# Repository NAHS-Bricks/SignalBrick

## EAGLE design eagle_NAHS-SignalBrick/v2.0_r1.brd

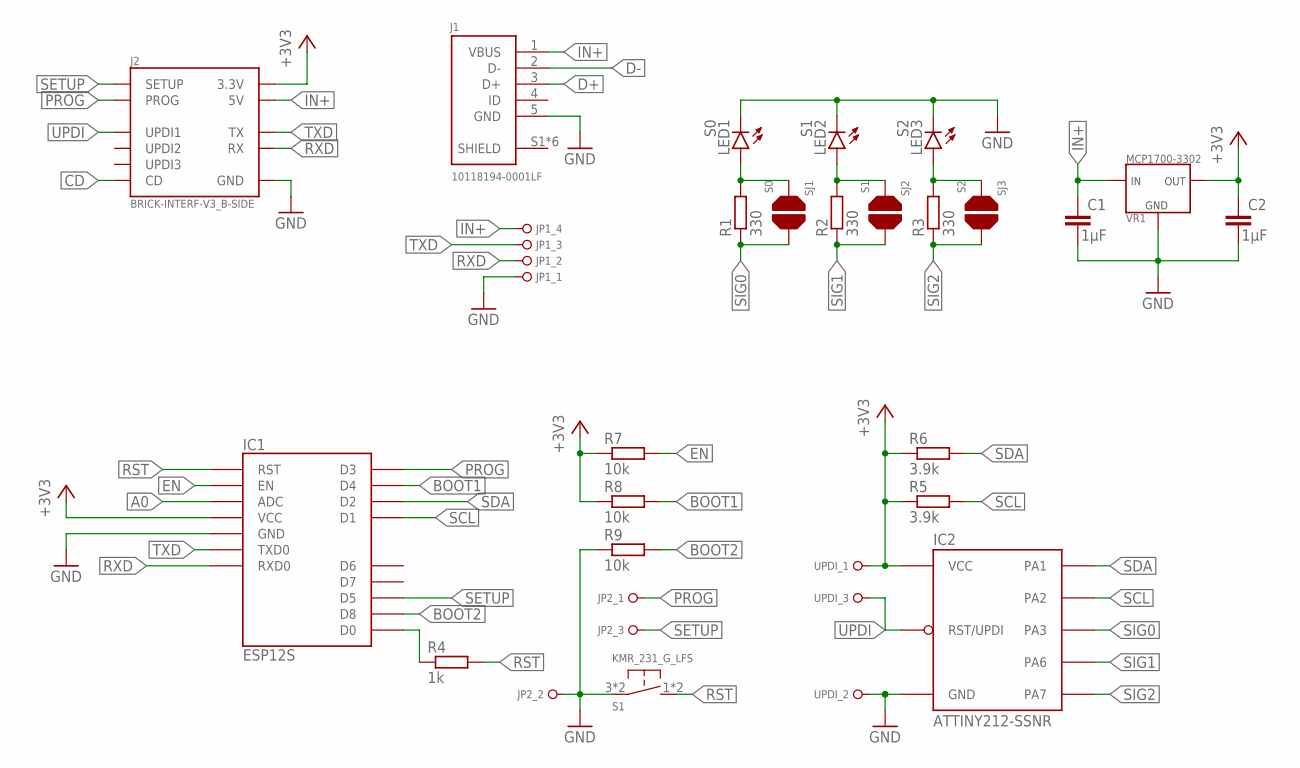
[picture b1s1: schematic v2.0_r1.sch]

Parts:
C1, C2: 1µF; C0805
IC1: ESP12S
IC2: ATTINY212-SSNR; SOIC8
J1: 10118194-0001LF
J2: BRICK-INTERF-V3_B-SIDE; DF9-11P-1V(32)
JP1: PINHD_1X04_R_1; 1X04_R_1
JP2: PINHD_1X03_R_1; 1X03_R_1
LED1: S0; LED5MM
LED2: S1; LED5MM
LED3: S2; LED5MM
R1, R2, R3: 330; R0603
R4: 1k; R0805
R5, R6: 3.9k; R0805
R7, R8, R9: 10k; R0805
S1: KMR_231_G_LFS
SJ1: S0; SOLDERJUMPER
SJ2: S1; SOLDERJUMPER
SJ3: S2; SOLDERJUMPER
UPDI: PINHD_1X03_R_1; 1X03_R_1
VR1: MCP1700-3302; SOT23

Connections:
+3V3: C2.1, IC1.VCC, IC2.1 (VCC), J2.10 (3.3V), R5.1, R6.1, R7.1, R8.1, UPDI.1, VR1.2 (OUT)
A0: IC1.ADC
BOOT1: IC1.GPIO2 (D4), R8.2
BOOT2: IC1.GPIO15 (D8), R9.2
CD: J2.5 (CD)
D+: J1.3 (D+)
D-: J1.2 (D-)
EN: IC1.EN, R7.2
GND: C1.2, C2.2, IC1.GND, IC2.8 (GND), J1.5 (GND), J2.6 (GND), JP1.1, JP2.2, LED1.K (C), LED2.K (C), LED3.K (C), R9.1, S1.3 (2), S1.4 (2), UPDI.2, VR1.1 (GND)
IN+: C1.1, J1.1 (VBUS), J2.4 (5V), JP1.4, VR1.3 (IN)
unnamed: LED1.A, R1.2, SJ1.1
unnamed: LED2.A, R2.2, SJ2.1
unnamed: LED3.A, R3.2, SJ3.1
PROG: IC1.GPIO0 (D3), J2.3 (PROG), JP2.1
RST: IC1.RST, R4.2, S1.1, S1.2 (1)
RXD: IC1.RXD0, J2.11 (RX), JP1.2
SCL: IC1.GPIO5 (D1), IC2.5 (PA2), R5.2
SDA: IC1.GPIO4 (D2), IC2.4 (PA1), R6.2
SETUP: IC1.GPIO14 (D5), J2.2 (SETUP), JP2.3
SHIELD: J1.S1 (SHIELD), J1.S2 (SHIELD), J1.S3 (SHIELD), J1.S4 (SHIELD), J1.S5 (SHIELD), J1.S6 (SHIELD)
SIG0: IC2.7 (PA3), R1.1, SJ1.2
SIG1: IC2.2 (PA6), R2.1, SJ2.2
SIG2: IC2.3 (PA7), R3.1, SJ3.2
TXD: IC1.TXD0, J2.1 (TX), JP1.3
UPDI: IC2.6 (RST/UPDI), J2.7 (UPDI1), UPDI.3
WAKE: IC1.GPIO16 (D0), R4.1

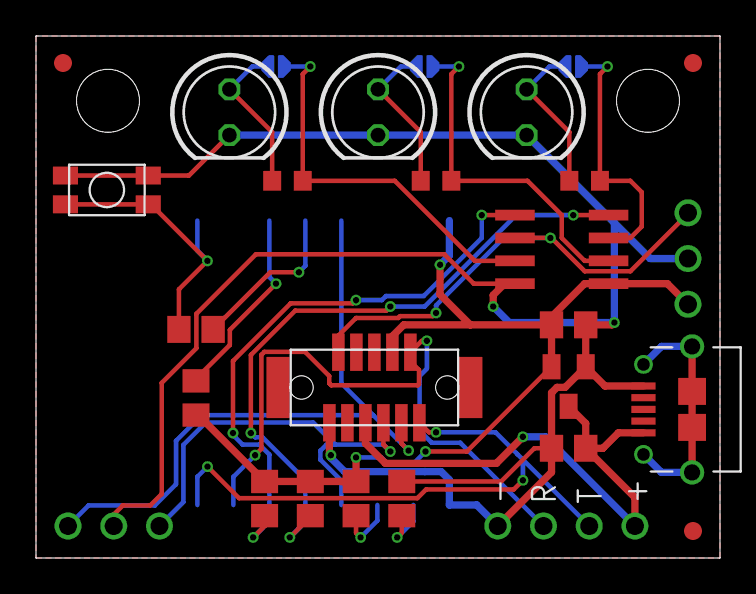
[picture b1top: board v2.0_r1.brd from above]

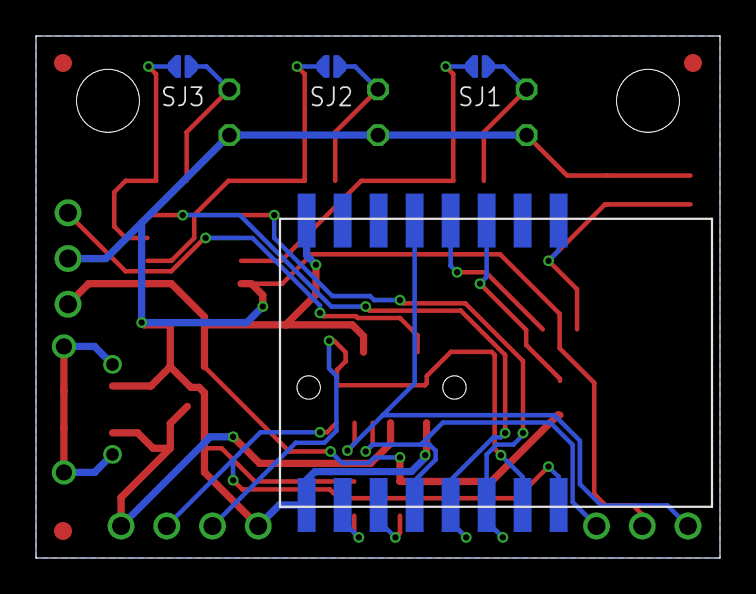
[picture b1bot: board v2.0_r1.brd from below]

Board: 2 copper layers, 38.0 x 29.0 mm, 30 parts (5 on the bottom side), 22 nets.

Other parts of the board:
FD1, FD2, FD3: FIDUCIAL
U$3: BRICKS_LOGO_10

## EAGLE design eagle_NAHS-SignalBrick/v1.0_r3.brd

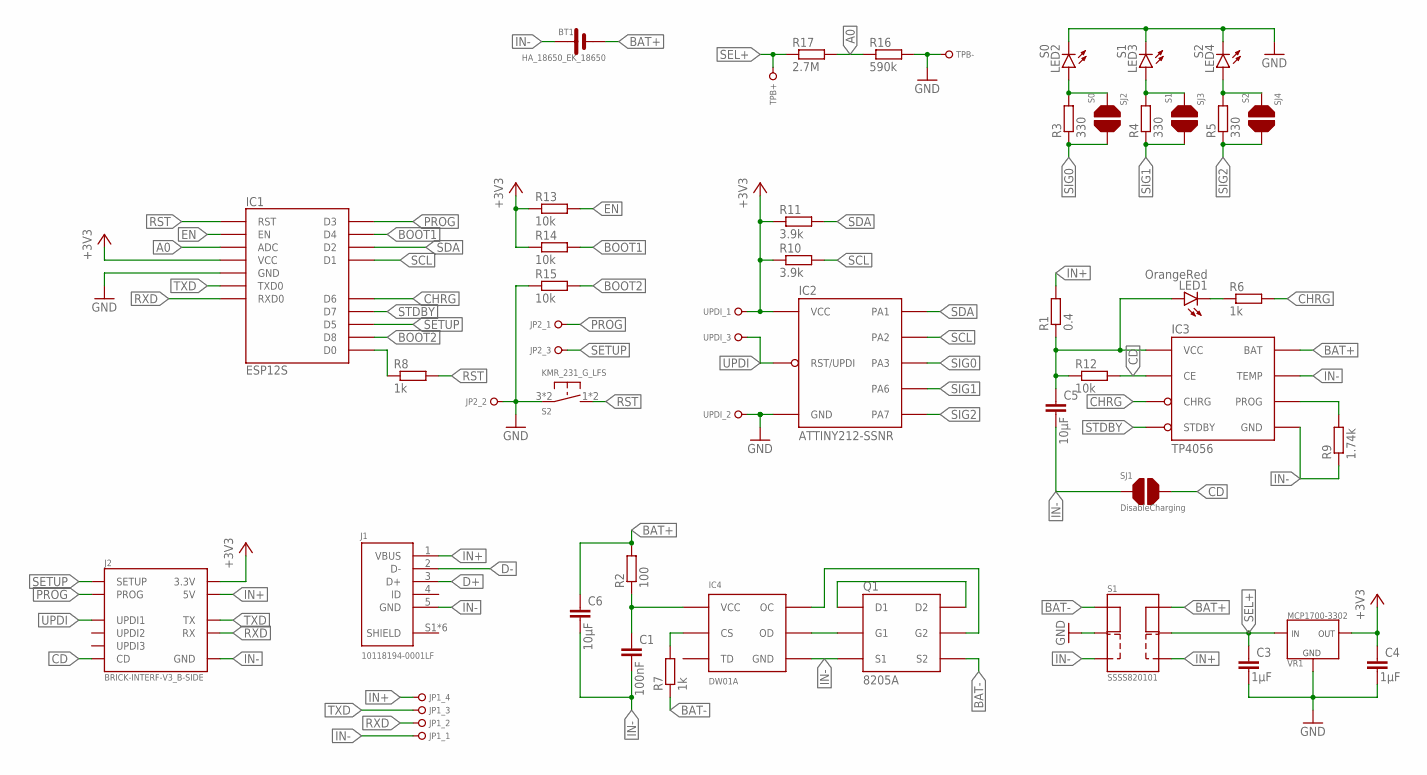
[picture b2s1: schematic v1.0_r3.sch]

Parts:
BT1: HA_18650_EK_18650
C1: 100nF; C0805
C3, C4: 1µF; C0805
C5, C6: 10µF; C0805
IC1: ESP12S
IC2: ATTINY212-SSNR; SOIC8
IC3: TP4056; SO8-THERMALPAD
IC4: DW01A; SOT23-6
J1: 10118194-0001LF
J2: BRICK-INTERF-V3_B-SIDE; DF9-11P-1V(32)
JP1: PINHD_1X04_R_1; 1X04_R_1
JP2: PINHD_1X03_R_1; 1X03_R_1
LED1: OrangeRed; CHIP-LED0805
LED2: S0; LED5MM
LED3: S1; LED5MM
LED4: S2; LED5MM
Q1: 8205A; TSSOP8
R1: 0.4; R0805
R2: 100; R0805
R3, R4, R5: 330; R0603
R6, R7, R8: 1k; R0805
R9: 1.74k; R0805
R10, R11: 3.9k; R0805
R12, R13, R14, R15: 10k; R0805
R16: 590k; R0805
R17: 2.7M; R0805
S1: SSSS820101
S2: KMR_231_G_LFS
SJ1: DisableCharging; SOLDERJUMPER
SJ2: S0; SOLDERJUMPER
SJ3: S1; SOLDERJUMPER
SJ4: S2; SOLDERJUMPER
TPB+: PINHD_1X01_S_0.8; 1X01_S_0.8
TPB-: PINHD_1X01_S_0.8; 1X01_S_0.8
UPDI: PINHD_1X03_R_1; 1X03_R_1
VR1: MCP1700-3302; SOT23

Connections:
+3V3: C4.1, IC1.VCC, IC2.1 (VCC), J2.10 (3.3V), R10.1, R11.1, R13.1, R14.1, UPDI.1, VR1.2 (OUT)
A0: IC1.ADC, R16.1, R17.2
BAT+: BT1.P1 (PLUS), BT1.P2 (PLUS), BT1.P3 (PLUS), C6.1, IC3.5 (BAT), R2.2, S1.6
BAT-: Q1.6 (S2), Q1.7 (S2), R7.1, S1.3
BOOT1: IC1.GPIO2 (D4), R14.2
BOOT2: IC1.GPIO15 (D8), R15.2
CD: IC3.8 (CE), J2.5 (CD), R12.2, SJ1.2
CHRG: IC1.GPIO12 (D6), IC3.7 (CHRG), R6.2
D+: J1.3 (D+)
D-: J1.2 (D-)
EN: IC1.EN, R13.2
GND: C3.2, C4.2, IC1.GND, IC2.8 (GND), JP2.2, LED2.K (C), LED3.K (C), LED4.K (C), R15.1, R16.2, S1.2, S2.3 (2), S2.4 (2), TPB-.1, UPDI.2, VR1.1 (GND)
IN+: J1.1 (VBUS), J2.4 (5V), JP1.4, R1.2, S1.4
IN-: BT1.M1 (MINUS), BT1.M2 (MINUS), BT1.M3 (MINUS), C1.2, C5.2, C6.2, IC3.1 (TEMP), IC3.3 (GND), IC3.T1 (GND), IC3.T2 (GND), IC3.T3 (GND), IC3.T4 (GND), IC3.T5 (GND), IC3.T6 (GND), IC3.T7 (GND), IC3.T8 (GND), IC4.6 (GND), J1.5 (GND), J2.6 (GND), JP1.1, Q1.2 (S1), Q1.3 (S1), R9.1, S1.1, SJ1.1
unnamed: C5.1, IC3.4 (VCC), LED1.A, R1.1, R12.1
unnamed: IC3.2 (PROG), R9.2
unnamed: IC4.2 (CS), R7.2
unnamed: C1.1, IC4.5 (VCC), R2.1
unnamed: LED2.A, R3.2, SJ2.1
unnamed: LED3.A, R4.2, SJ3.1
unnamed: LED1.C, R6.1
unnamed: IC4.1 (OD), Q1.4 (G1)
unnamed: LED4.A, R5.2, SJ4.1
unnamed: Q1.1 (D1), Q1.8 (D2)
unnamed: IC4.3 (OC), Q1.5 (G2)
PROG: IC1.GPIO0 (D3), J2.3 (PROG), JP2.1
RST: IC1.RST, R8.2, S2.1, S2.2 (1)
RXD: IC1.RXD0, J2.11 (RX), JP1.2
SCL: IC1.GPIO5 (D1), IC2.5 (PA2), R10.2
SDA: IC1.GPIO4 (D2), IC2.4 (PA1), R11.2
SEL+: C3.1, R17.1, S1.5, TPB+.1, VR1.3 (IN)
SETUP: IC1.GPIO14 (D5), J2.2 (SETUP), JP2.3
SHIELD: J1.S1 (SHIELD), J1.S2 (SHIELD), J1.S3 (SHIELD), J1.S4 (SHIELD), J1.S5 (SHIELD), J1.S6 (SHIELD)
SIG0: IC2.7 (PA3), R3.1, SJ2.2
SIG1: IC2.2 (PA6), R4.1, SJ3.2
SIG2: IC2.3 (PA7), R5.1, SJ4.2
STDBY: IC1.GPIO13 (D7), IC3.6 (STDBY)
TXD: IC1.TXD0, J2.1 (TX), JP1.3
UPDI: IC2.6 (RST/UPDI), J2.7 (UPDI1), UPDI.3
WAKE: IC1.GPIO16 (D0), R8.1

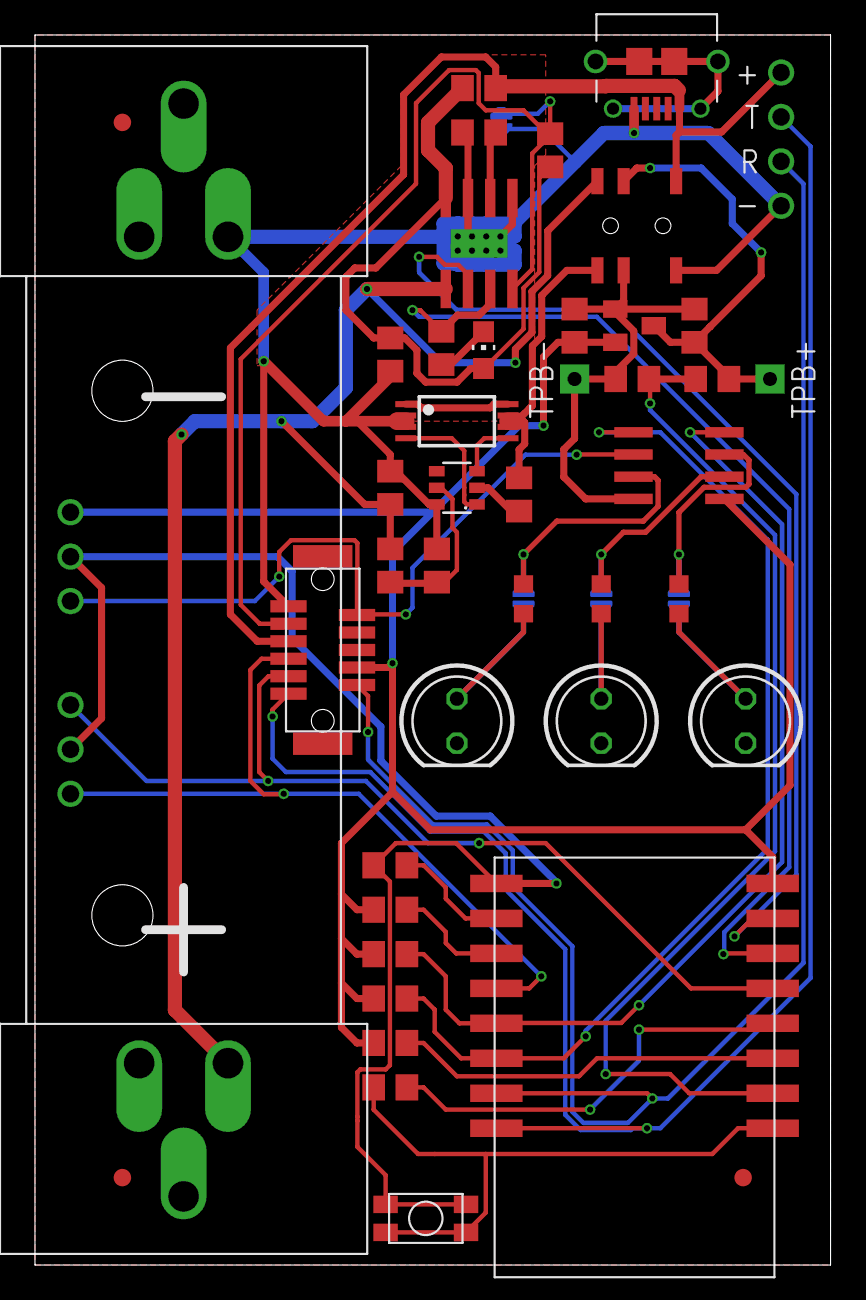
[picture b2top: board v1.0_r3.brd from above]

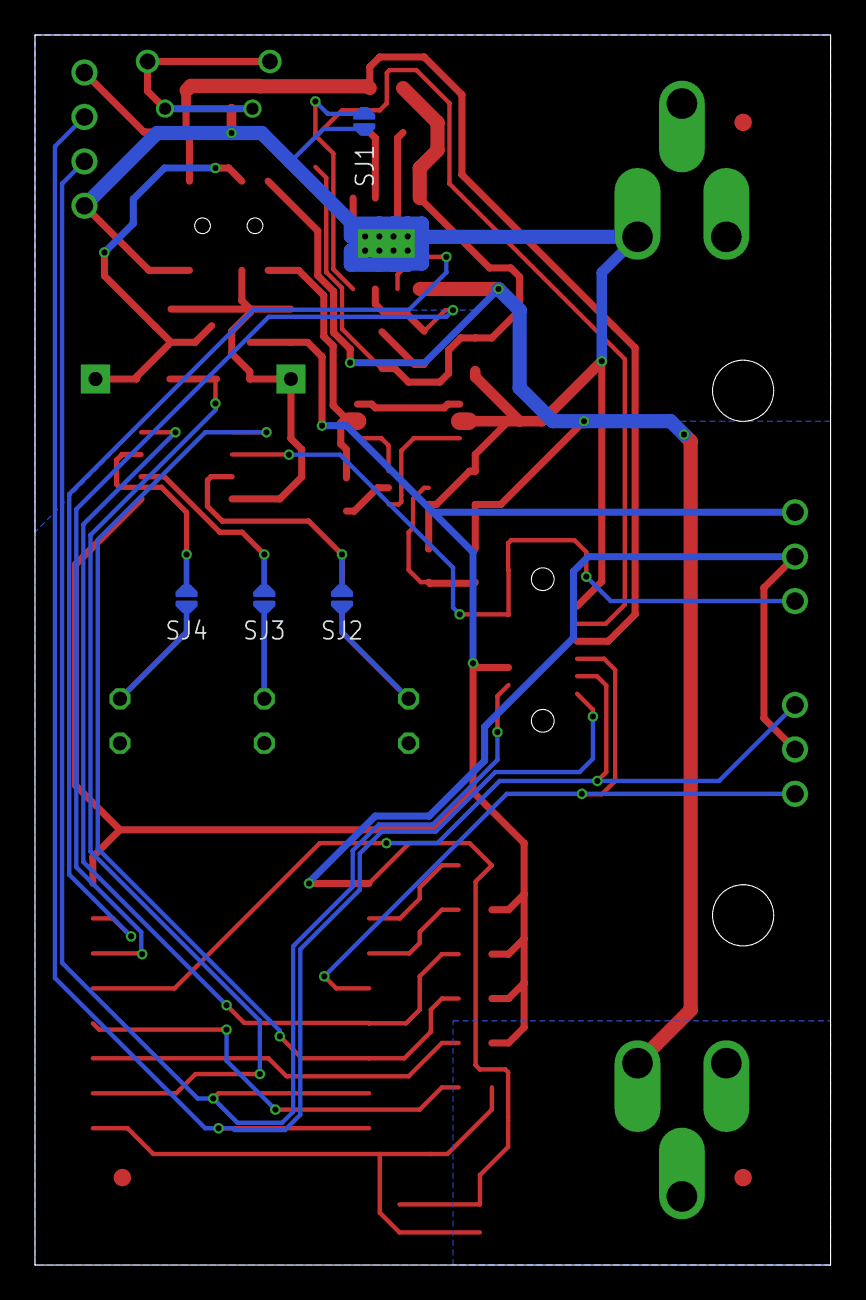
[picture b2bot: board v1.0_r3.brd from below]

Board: 2 copper layers, 45.5 x 70.3 mm, 50 parts (5 on the bottom side), 38 nets.

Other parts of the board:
FD1, FD2, FD3: FIDUCIAL
U$1: BRICKS_LOGO_20

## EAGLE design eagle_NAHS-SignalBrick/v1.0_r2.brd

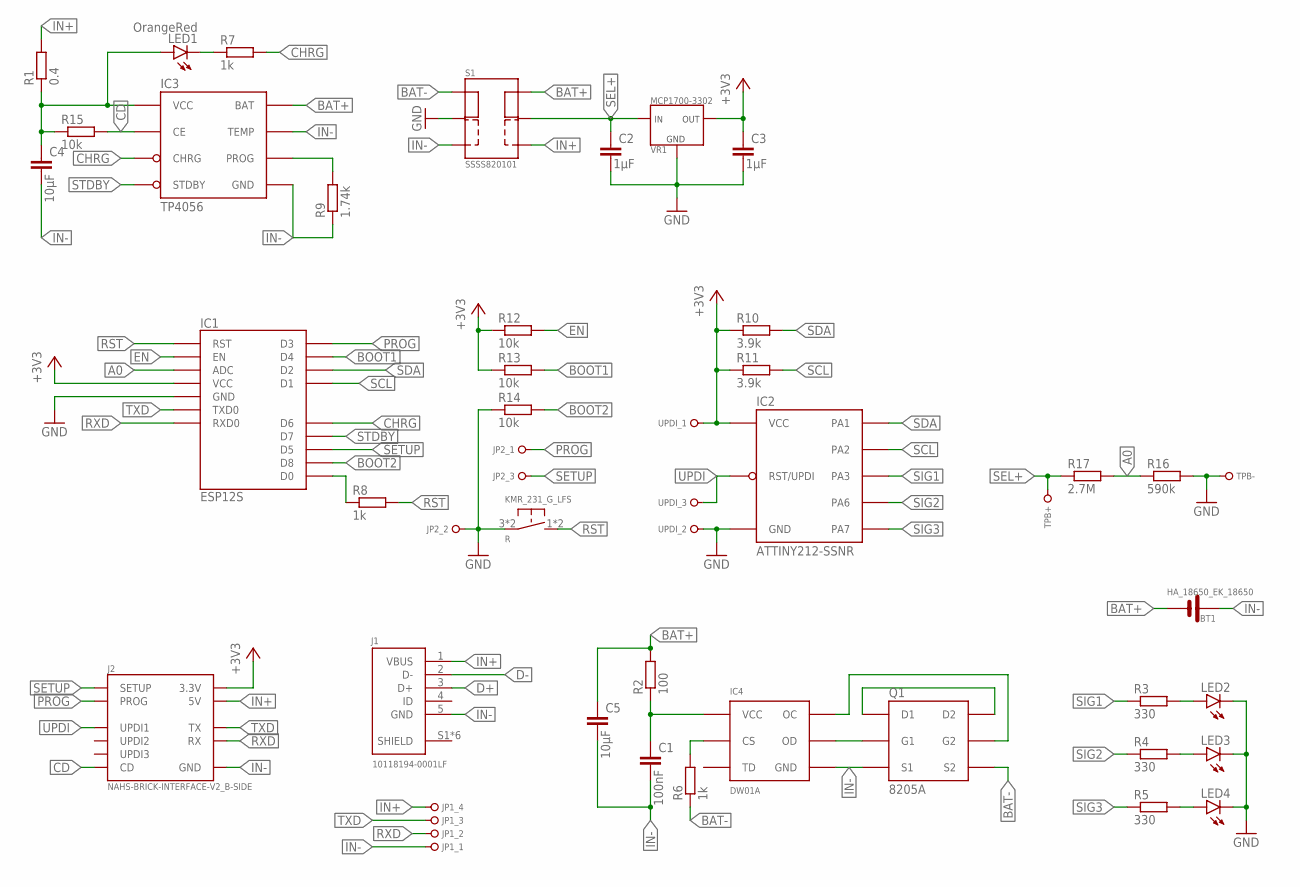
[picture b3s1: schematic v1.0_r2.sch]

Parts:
BT1: HA_18650_EK_18650
C1: 100nF; C0805
C2, C3: 1µF; C0805
C4, C5: 10µF; C0805
IC1: ESP12S
IC2: ATTINY212-SSNR; SOIC8
IC3: TP4056; SO8-THERMALPAD
IC4: DW01A; SOT23-6
J1: 10118194-0001LF
J2: NAHS-BRICK-INTERFACE-V2_B-SIDE; 500334-0160-V2
JP1: PINHD_1X04_R_1; 1X04_R_1
JP2: PINHD_1X03_R_1; 1X03_R_1
LED1: OrangeRed; CHIP-LED0805
LED2, LED3, LED4: LED5MM
Q1: 8205A; TSSOP8
R: KMR_231_G_LFS
R1: 0.4; R0805
R2: 100; R0805
R3, R4, R5: 330; R0603
R6, R7, R8: 1k; R0805
R9: 1.74k; R0805
R10, R11: 3.9k; R0805
R12, R13, R14, R15: 10k; R0805
R16: 590k; R0805
R17: 2.7M; R0805
S1: SSSS820101
TPB+: PINHD_1X01_S_0.8; 1X01_S_0.8
TPB-: PINHD_1X01_S_0.8; 1X01_S_0.8
UPDI: PINHD_1X03_R_1; 1X03_R_1
VR1: MCP1700-3302; SOT23

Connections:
+3V3: C3.1, IC1.VCC, IC2.1 (VCC), J2.9 (3.3V), R10.1, R11.1, R12.1, R13.1, UPDI.1, VR1.2 (OUT)
A0: IC1.ADC, R16.1, R17.2
BAT+: BT1.P1 (PLUS), BT1.P2 (PLUS), BT1.P3 (PLUS), C5.1, IC3.5 (BAT), R2.2, S1.6
BAT-: Q1.6 (S2), Q1.7 (S2), R6.1, S1.3
BOOT1: IC1.GPIO2 (D4), R13.2
BOOT2: IC1.GPIO15 (D8), R14.2
CD: IC3.8 (CE), J2.13 (CD), R15.2
CHRG: IC1.GPIO12 (D6), IC3.7 (CHRG), R7.2
D+: J1.3 (D+)
D-: J1.2 (D-)
EN: IC1.EN, R12.2
GND: C2.2, C3.2, IC1.GND, IC2.8 (GND), JP2.2, LED2.K (C), LED3.K (C), LED4.K (C), R.3 (2), R.4 (2), R14.1, R16.2, S1.2, TPB-.1, UPDI.2, VR1.1 (GND)
IN+: J1.1 (VBUS), J2.1 (5V), J2.2 (5V), J2.3 (5V), JP1.4, R1.2, S1.4
IN-: BT1.M1 (MINUS), BT1.M2 (MINUS), BT1.M3 (MINUS), C1.2, C4.2, C5.2, IC3.1 (TEMP), IC3.3 (GND), IC3.T1 (GND), IC3.T2 (GND), IC3.T3 (GND), IC3.T4 (GND), IC3.T5 (GND), IC3.T6 (GND), IC3.T7 (GND), IC3.T8 (GND), IC4.6 (GND), J1.5 (GND), J2.14 (GND), J2.15 (GND), J2.16 (GND), JP1.1, Q1.2 (S1), Q1.3 (S1), R9.1, S1.1
unnamed: C4.1, IC3.4 (VCC), LED1.A, R1.1, R15.1
unnamed: IC3.2 (PROG), R9.2
unnamed: IC4.2 (CS), R6.2
unnamed: C1.1, IC4.5 (VCC), R2.1
unnamed: LED2.A, R3.2
unnamed: LED3.A, R4.2
unnamed: LED1.C, R7.1
unnamed: IC4.1 (OD), Q1.4 (G1)
unnamed: LED4.A, R5.2
unnamed: Q1.1 (D1), Q1.8 (D2)
unnamed: IC4.3 (OC), Q1.5 (G2)
PROG: IC1.GPIO0 (D3), J2.7 (PROG), JP2.1
RST: IC1.RST, R.1, R.2 (1), R8.2
RXD: IC1.RXD0, J2.6 (RX), JP1.2
SCL: IC1.GPIO5 (D1), IC2.5 (PA2), R11.2
SDA: IC1.GPIO4 (D2), IC2.4 (PA1), R10.2
SEL+: C2.1, R17.1, S1.5, TPB+.1, VR1.3 (IN)
SETUP: IC1.GPIO14 (D5), J2.8 (SETUP), JP2.3
SHIELD: J1.S1 (SHIELD), J1.S2 (SHIELD), J1.S3 (SHIELD), J1.S4 (SHIELD), J1.S5 (SHIELD), J1.S6 (SHIELD)
SIG1: IC2.7 (PA3), R3.1
SIG2: IC2.2 (PA6), R4.1
SIG3: IC2.3 (PA7), R5.1
STDBY: IC1.GPIO13 (D7), IC3.6 (STDBY)
TXD: IC1.TXD0, J2.5 (TX), JP1.3
UPDI: IC2.6 (RST/UPDI), J2.10 (UPDI1), UPDI.3
WAKE: IC1.GPIO16 (D0), R8.1

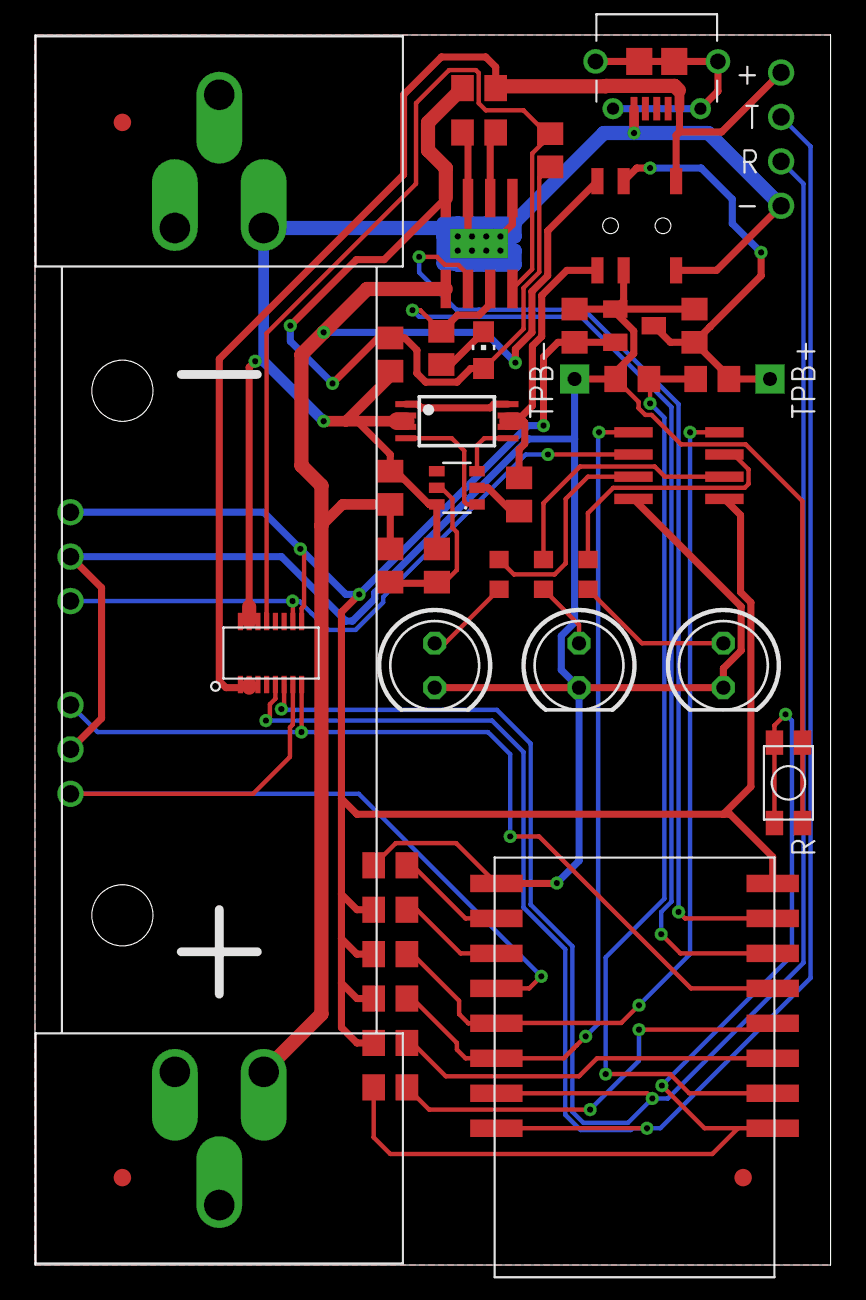
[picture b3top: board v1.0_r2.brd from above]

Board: 2 copper layers, 45.5 x 70.3 mm, 45 parts (0 on the bottom side), 38 nets.

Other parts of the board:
FD1, FD2, FD3: FIDUCIAL

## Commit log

2021-02-22 Boardlayout for v1.0 R1
2021-02-22 renamed components, finished for production
2021-05-08 Boardlayout for v1.0 R2 in progress
2021-05-09 Boardlayout for v1.0 R2
2021-05-20 Boardlayout v1.0 R2 - Send to JLCPCB
2021-06-18 added platformio project for nahs-SignalBrick_v1.0
2022-01-13 build-firmware invoker
2022-02-07 Board v1.0 R3 WIP
2022-02-09 Board v1.0 R3 done
2022-02-12 Board v2.0 R1 done
2022-02-12 added ibom invoker and ibom for v2.0 r1 board
2022-11-30 changed naming of platformio project; migrated from old to new libraries in firmware
2023-01-15 Board v1.0 R4 done
